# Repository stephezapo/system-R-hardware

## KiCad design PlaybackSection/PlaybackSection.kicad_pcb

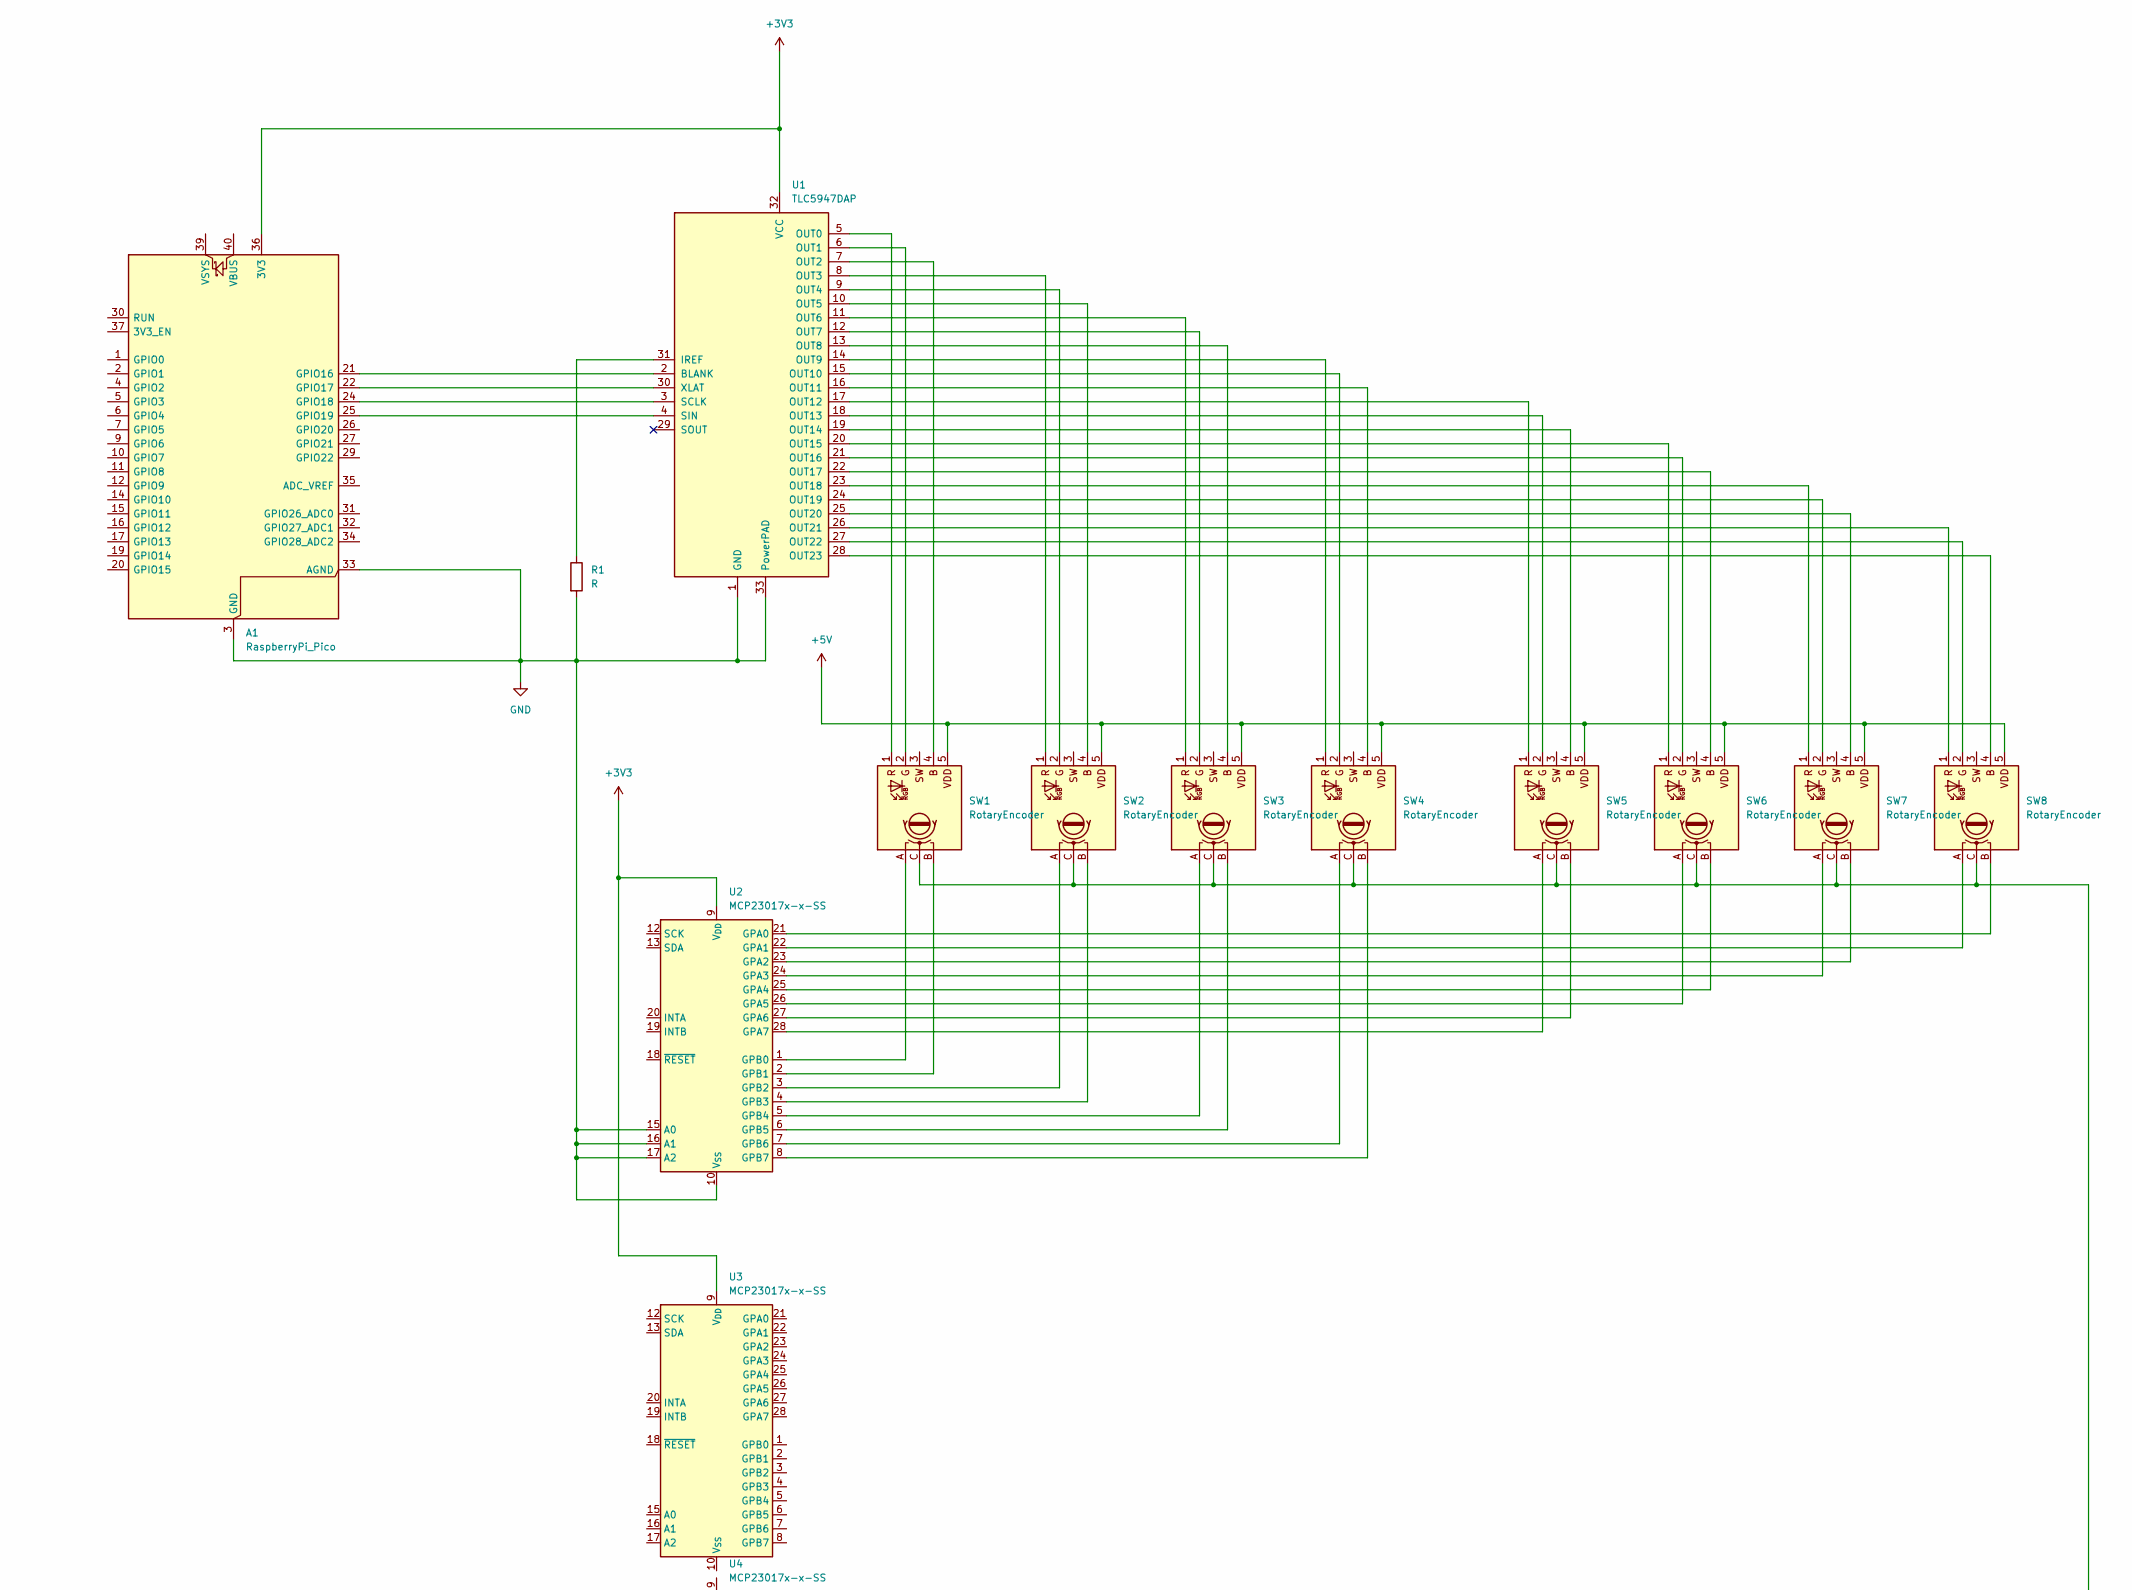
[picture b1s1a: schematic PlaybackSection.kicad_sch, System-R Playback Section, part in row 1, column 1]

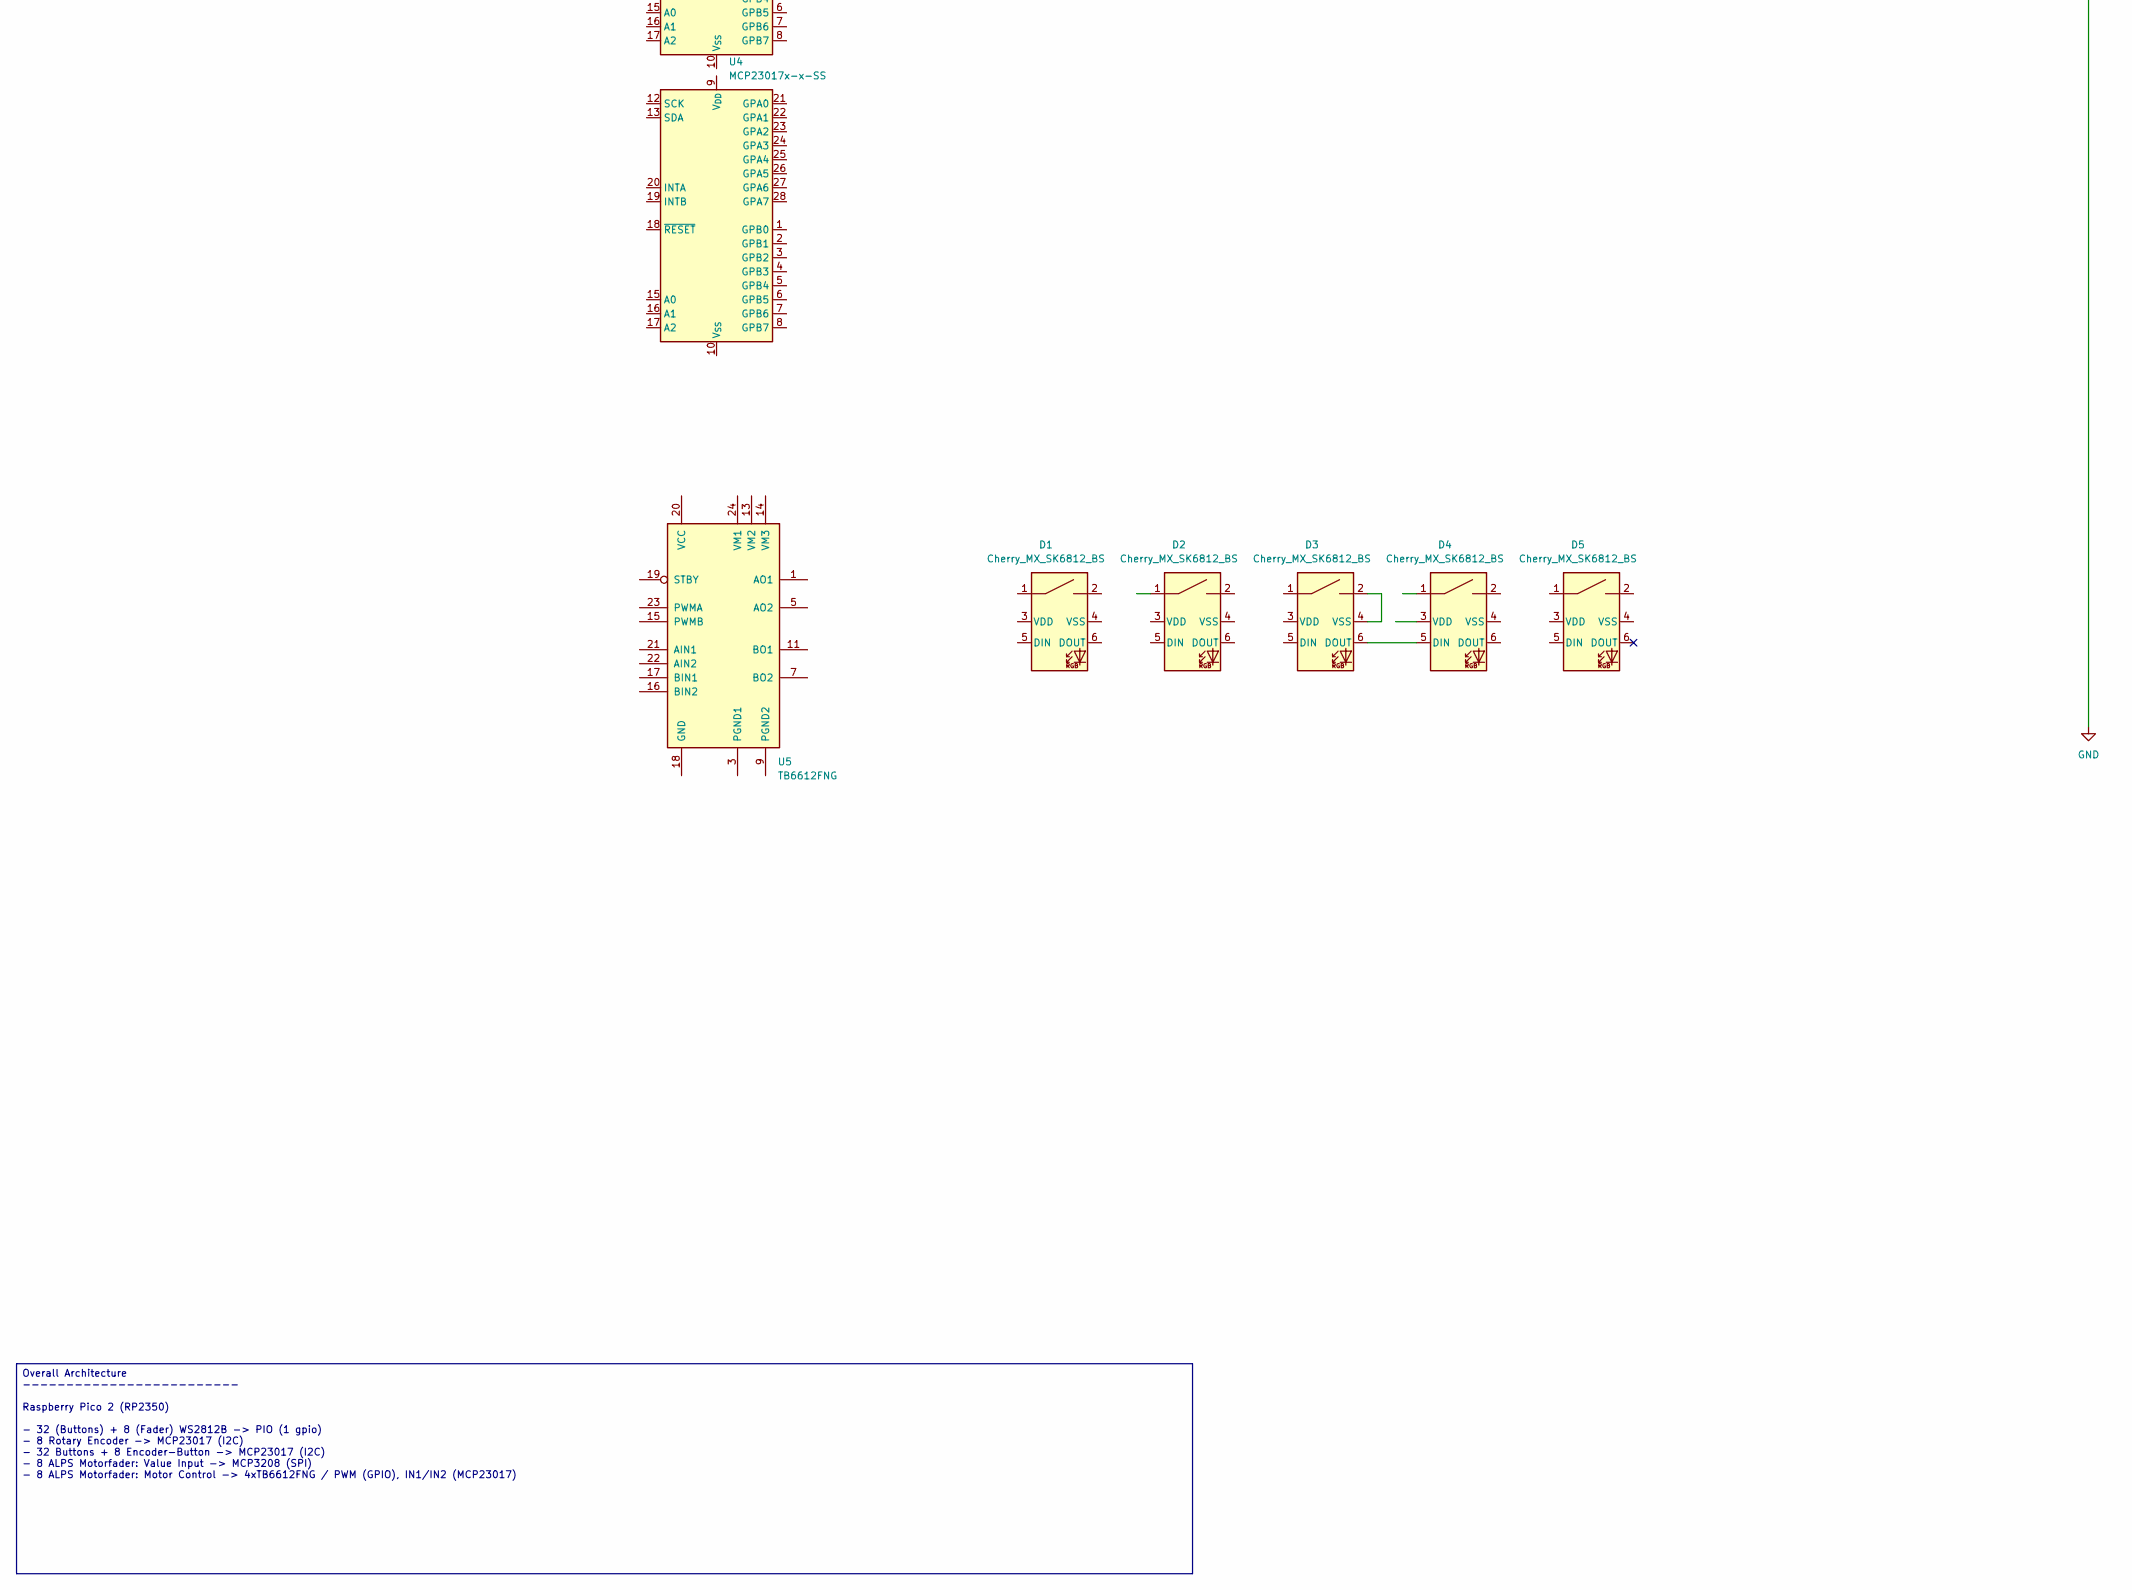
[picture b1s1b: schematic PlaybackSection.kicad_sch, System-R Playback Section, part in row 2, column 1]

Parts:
A1: RaspberryPi_Pico; RaspberryPi_Pico_Common_Unspecified
D1, D2, D3, D4, D5: Cherry_MX_SK6812_BS
R1: R
SW1, SW2, SW3, SW4, SW5, SW6, SW7, SW8: RotaryEncoder; EC12PLRGB_Rotary_Encoder
U1: TLC5947DAP; HTSSOP-32-1EP_6.1x11mm_P0.65mm_EP5.2x11mm_Mask4.11x4.36mm_T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
U2, U3, U4: MCP23017x-x-SS; SSOP-28_5.3x10.2mm_P0.65mm
U5: TB6612FNG; SSOP-24_5.3x8.2mm_P0.65mm

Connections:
+3V3: A1.36 (3V3), U1.32 (VCC), U2.9 (V_{DD}), U3.9 (V_{DD}_9)
+5V: SW1.5 (VDD), SW2.5 (VDD), SW3.5 (VDD), SW4.5 (VDD), SW5.5 (VDD), SW6.5 (VDD), SW7.5 (VDD), SW8.5 (VDD)
GND: A1.3 (GND), A1.8 (GND), A1.13 (GND), A1.18 (GND), A1.23 (GND), A1.28 (GND), A1.33 (AGND), A1.38 (GND), R1.2, SW1.C, SW2.C, SW3.C, SW4.C, SW5.C, SW6.C, SW7.C, SW8.C, U1.1 (GND), U1.33 (PowerPAD), U2.10 (V_{SS}), U2.15 (A0), U2.16 (A1), U2.17 (A2)
unnamed: A1.21 (GPIO16), U1.2 (BLANK)
unnamed: A1.22 (GPIO17), U1.30 (XLAT)
unnamed: A1.24 (GPIO18), U1.3 (SCLK)
unnamed: A1.25 (GPIO19), U1.4 (SIN)
unnamed: D3.6 (DOUT), D4.5 (DIN_5)
unnamed: D3.2, D3.4 (VSS)
unnamed: SW1.2 (G), U1.6 (OUT1)
unnamed: SW1.1 (R), U1.5 (OUT0)
unnamed: SW2.2 (G), U1.9 (OUT4)
unnamed: SW2.1 (R), U1.8 (OUT3)
unnamed: SW3.2 (G), U1.12 (OUT7)
unnamed: SW3.1 (R), U1.11 (OUT6)
unnamed: SW4.2 (G), U1.15 (OUT10)
unnamed: SW4.1 (R), U1.14 (OUT9)
unnamed: SW5.2 (G), U1.18 (OUT13)
unnamed: SW5.1 (R), U1.17 (OUT12)
unnamed: SW6.2 (G), U1.21 (OUT16)
unnamed: SW6.1 (R), U1.20 (OUT15)
unnamed: SW7.2 (G), U1.24 (OUT19)
unnamed: SW7.1 (R), U1.23 (OUT18)
unnamed: SW8.2 (G), U1.27 (OUT22)
unnamed: SW8.1 (R), U1.26 (OUT21)
unnamed: R1.1, U1.31 (IREF)
unnamed: SW1.4 (B), U1.7 (OUT2)
unnamed: SW2.4 (B), U1.10 (OUT5)
unnamed: SW3.4 (B), U1.13 (OUT8)
unnamed: SW4.4 (B), U1.16 (OUT11)
unnamed: SW5.4 (B), U1.19 (OUT14)
unnamed: SW6.4 (B), U1.22 (OUT17)
unnamed: SW7.4 (B), U1.25 (OUT20)
unnamed: SW8.4 (B), U1.28 (OUT23)
unnamed: SW8.B, U2.21 (GPA0)
unnamed: SW8.A, U2.22 (GPA1)
unnamed: SW7.B, U2.23 (GPA2)
unnamed: SW7.A, U2.24 (GPA3)
unnamed: SW6.B, U2.25 (GPA4)
unnamed: SW6.A, U2.26 (GPA5)
unnamed: SW5.B, U2.27 (GPA6)
unnamed: SW5.A, U2.28 (GPA7)
unnamed: SW1.A, U2.1 (GPB0)
unnamed: SW1.B, U2.2 (GPB1)
unnamed: SW2.A, U2.3 (GPB2)
unnamed: SW2.B, U2.4 (GPB3)
unnamed: SW3.A, U2.5 (GPB4)
unnamed: SW3.B, U2.6 (GPB5)
unnamed: SW4.A, U2.7 (GPB6)
unnamed: SW4.B, U2.8 (GPB7)
unnamed: U5.1 (AO1), U5.2 (AO1)
unnamed: U5.5 (AO2), U5.6 (AO2)
unnamed: U5.11 (BO1), U5.12 (BO1)
unnamed: U5.7 (BO2), U5.8 (BO2)
unnamed: U5.3 (PGND1), U5.4 (PGND1)
unnamed: U5.9 (PGND2), U5.10 (PGND2)

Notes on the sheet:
Overall Architecture ------------------------- Raspberry Pico 2 (RP2350) - 32 (Buttons) + 8 (Fader) WS2812B -> PIO (1 gpio) - 8 Rotary Encoder -> MCP23017 (I2C) - 32 Buttons + 8 Encoder-Button -> MCP23017 (I2C) - 8 ALPS Motorfader: Value Input -> MCP3208 (SPI) - 8 ALPS Motorfader: Motor Control -> 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

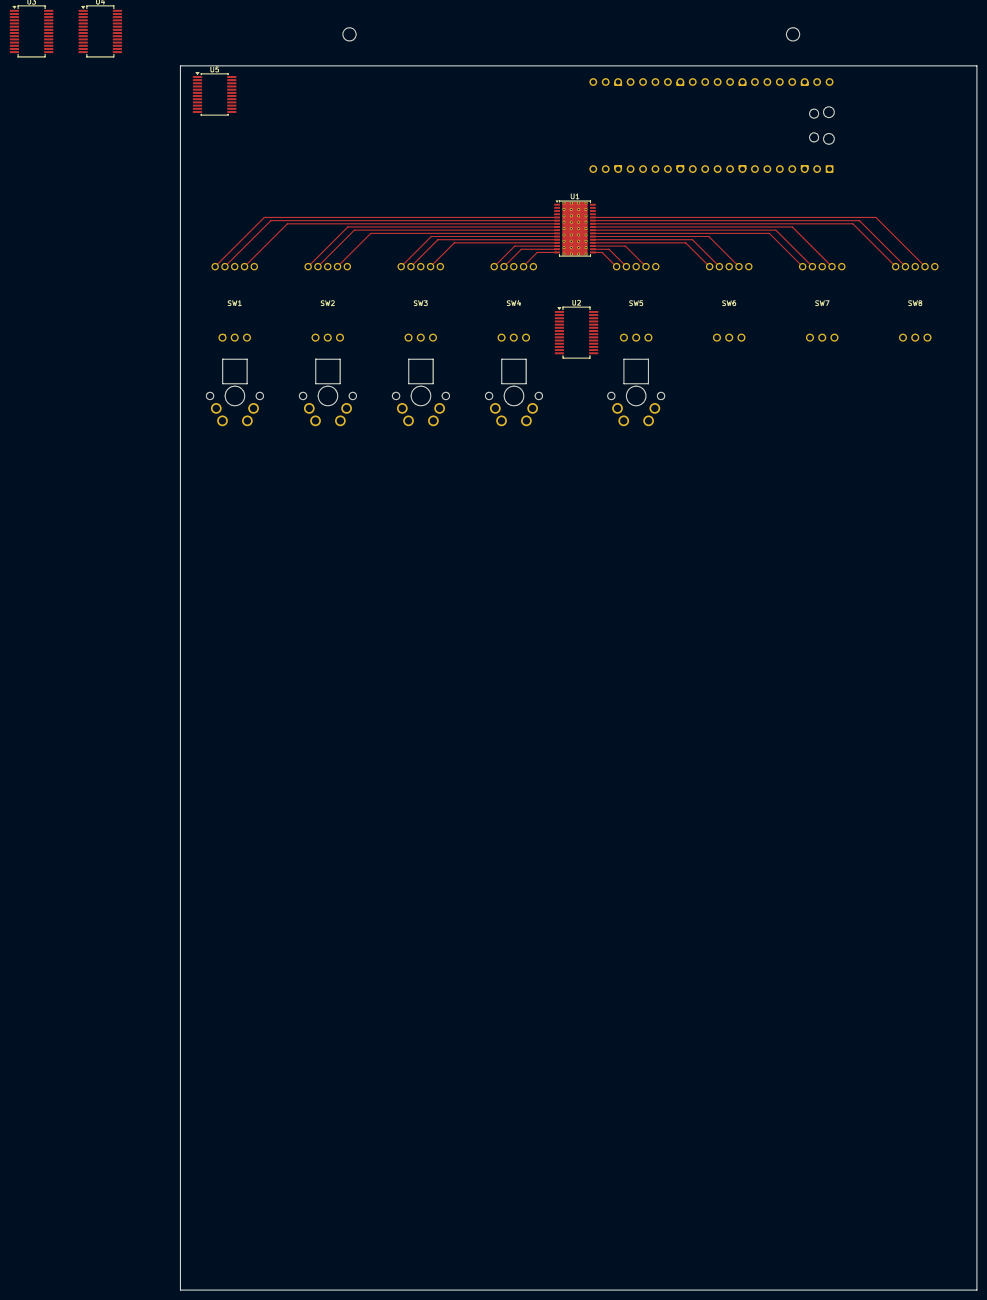
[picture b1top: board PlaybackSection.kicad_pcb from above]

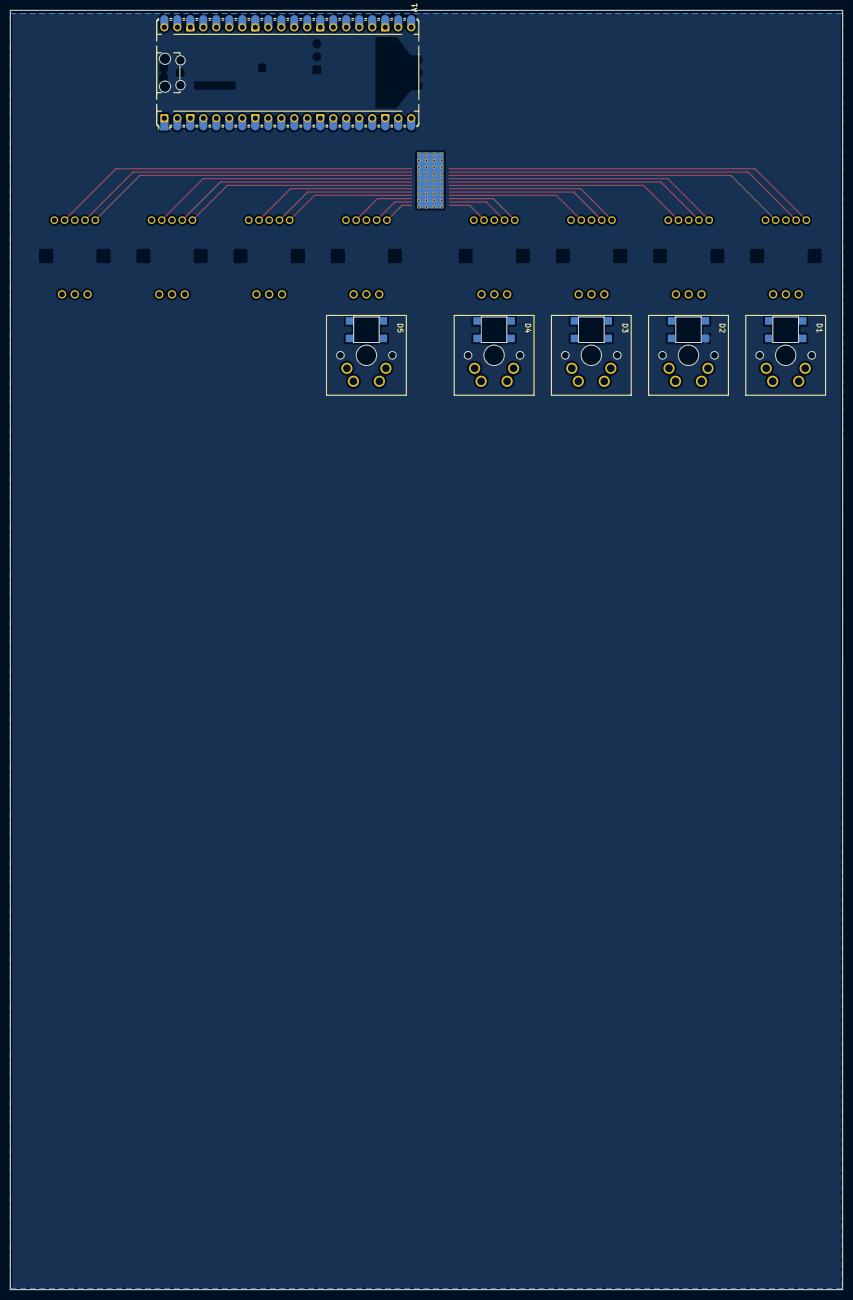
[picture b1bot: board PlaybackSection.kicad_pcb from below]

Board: 2 copper layers, 162.7 x 250.1 mm, 19 parts (6 on the bottom side), 55 nets.

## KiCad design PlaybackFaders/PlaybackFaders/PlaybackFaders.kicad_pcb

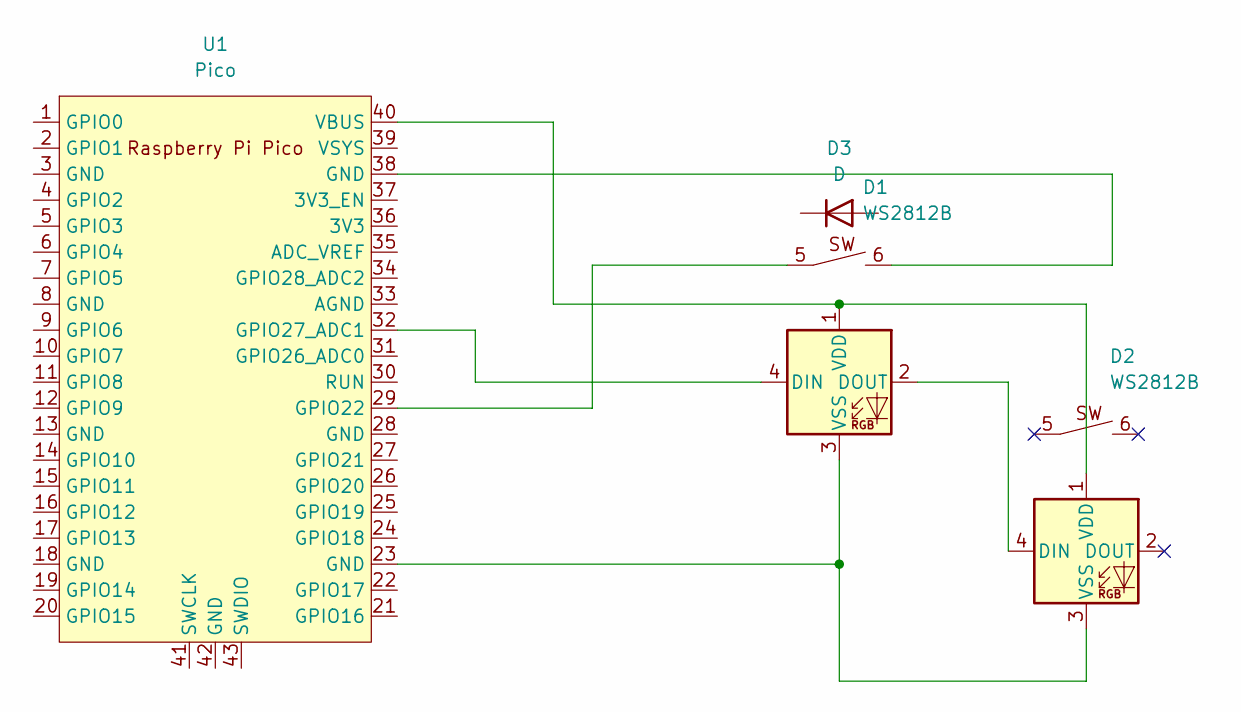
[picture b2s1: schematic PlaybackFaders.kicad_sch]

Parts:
D1, D2: WS2812B; Cherry_MX_SK6812_BS
D3: D; D_A-405_P7.62mm_Horizontal
U1: Pico; RPi_Pico_SMD_TH

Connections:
unnamed: D1.4 (DIN), U1.32 (GPIO27_ADC1)
unnamed: D1.2 (DOUT), D2.4 (DIN)
unnamed: D1.6, U1.38 (GND)
unnamed: D1.1 (VDD), D2.1 (VDD), U1.40 (VBUS)
unnamed: D1.3 (VSS), D2.3 (VSS), U1.23 (GND)
unnamed: D1.5, U1.29 (GPIO22)

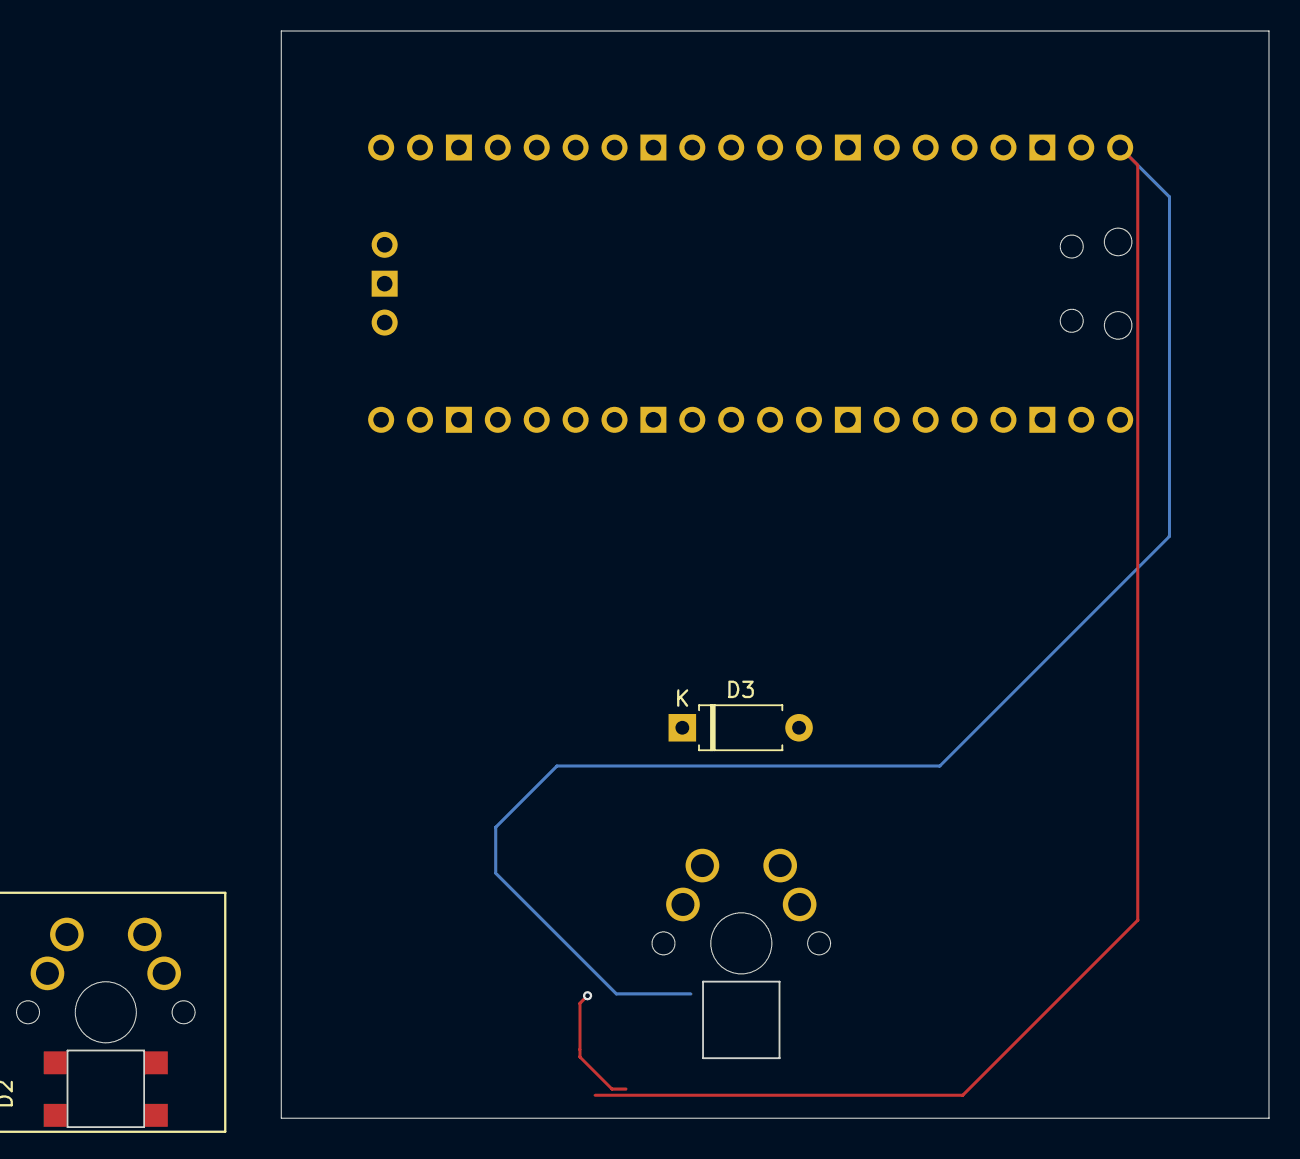
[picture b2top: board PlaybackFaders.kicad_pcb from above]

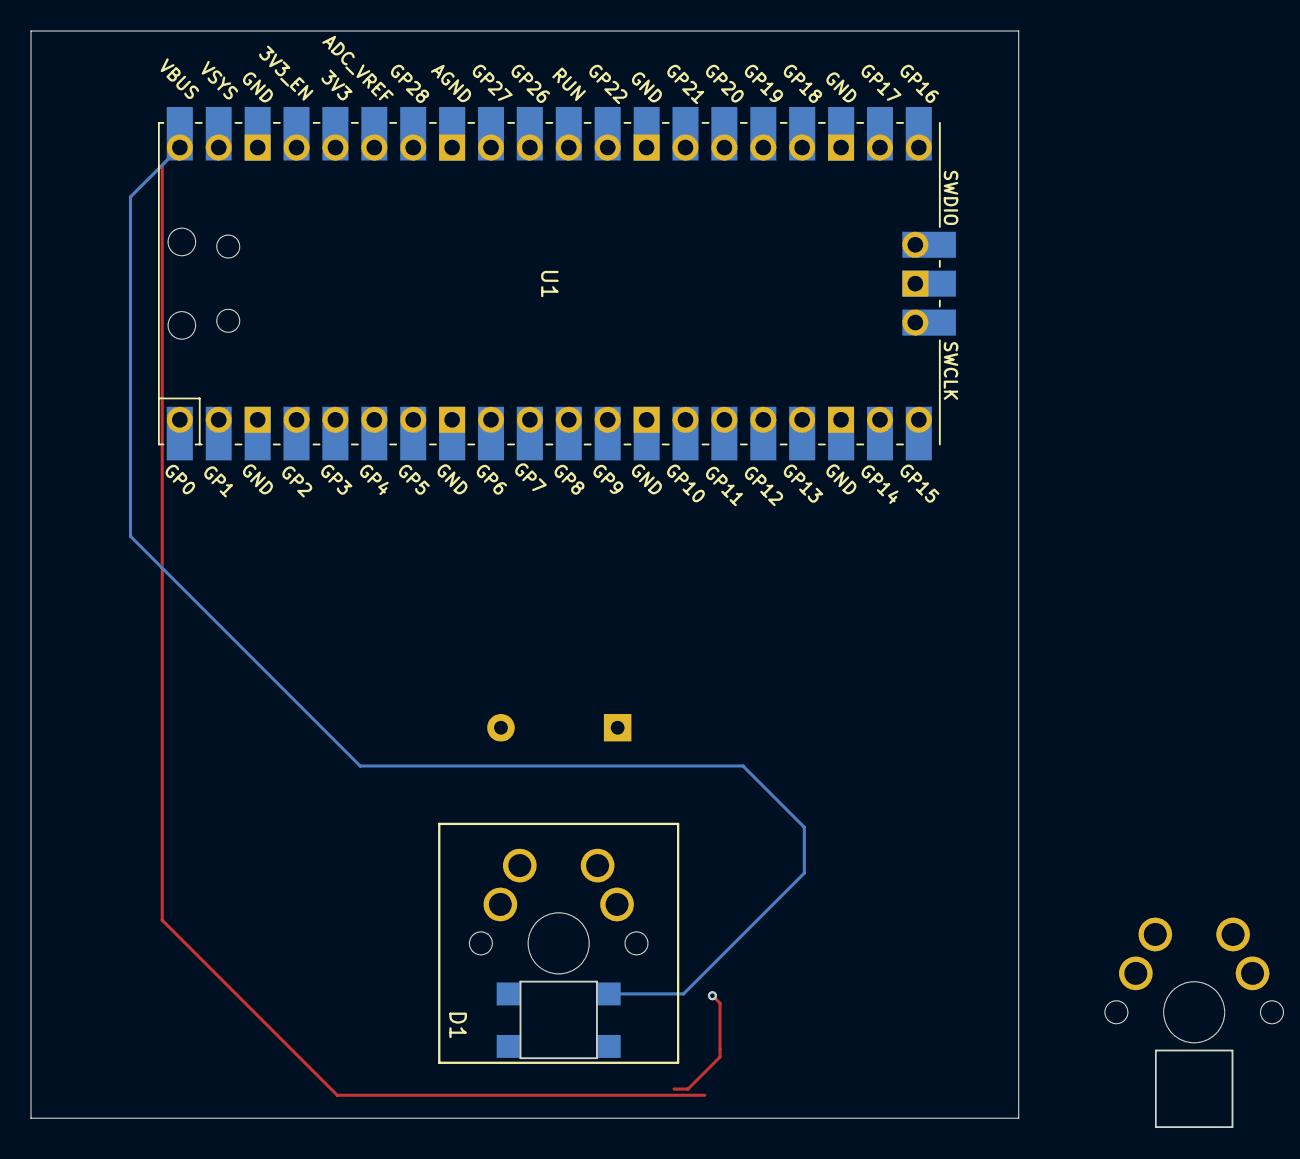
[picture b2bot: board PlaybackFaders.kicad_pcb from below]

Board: 2 copper layers, 78.5 x 71.6 mm, 4 parts (2 on the bottom side), 6 nets.

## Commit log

2024-04-29 Added Raspberry Pico Schematic, Footprint and 3D model (project-based)
2024-04-30 CherryMX-WS2812 added with custom symbol
2024-05-04 Fixed CherryMX-WS2812 pin mapping
2026-05-13 console layout first draft
2026-05-17 Draw.io console layout with 2 RPi displays plus extension
2026-05-20 firmware WIP (tlc5947), board WIP
2026-05-22 continued wiring for tlc5947 and mcp23017
